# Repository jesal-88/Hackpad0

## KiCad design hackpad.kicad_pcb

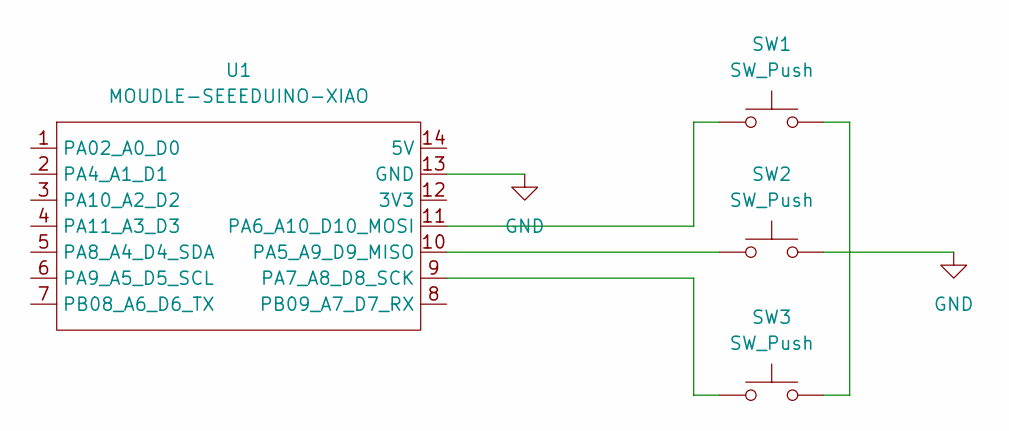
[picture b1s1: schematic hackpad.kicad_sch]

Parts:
SW1, SW2, SW3: SW_Push; SW_Cherry_MX_1.00u_PCB
U1: MOUDLE-SEEEDUINO-XIAO; XIAO-Generic-Hybrid-14P-2.54-21X17.8MM

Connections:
GND: SW2.2, U1.13 (GND)
unnamed: SW1.2, SW3.2
unnamed: SW2.1, U1.10 (PA5_A9_D9_MISO)
unnamed: SW1.1, U1.11 (PA6_A10_D10_MOSI)
unnamed: SW3.1, U1.9 (PA7_A8_D8_SCK)

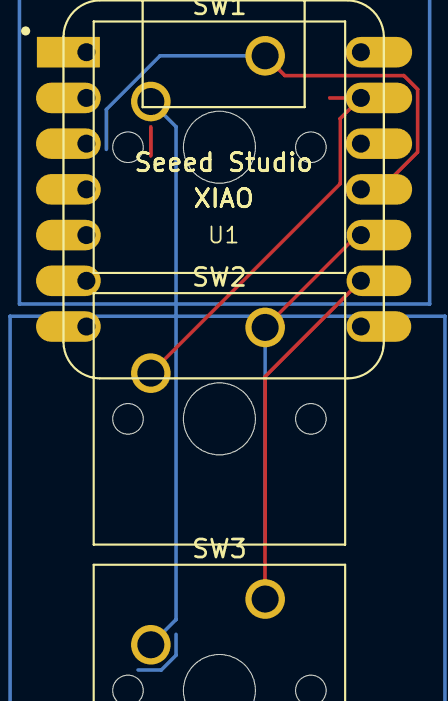
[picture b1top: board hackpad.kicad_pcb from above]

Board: 2 copper layers, 4 parts (0 on the bottom side), 5 nets.
